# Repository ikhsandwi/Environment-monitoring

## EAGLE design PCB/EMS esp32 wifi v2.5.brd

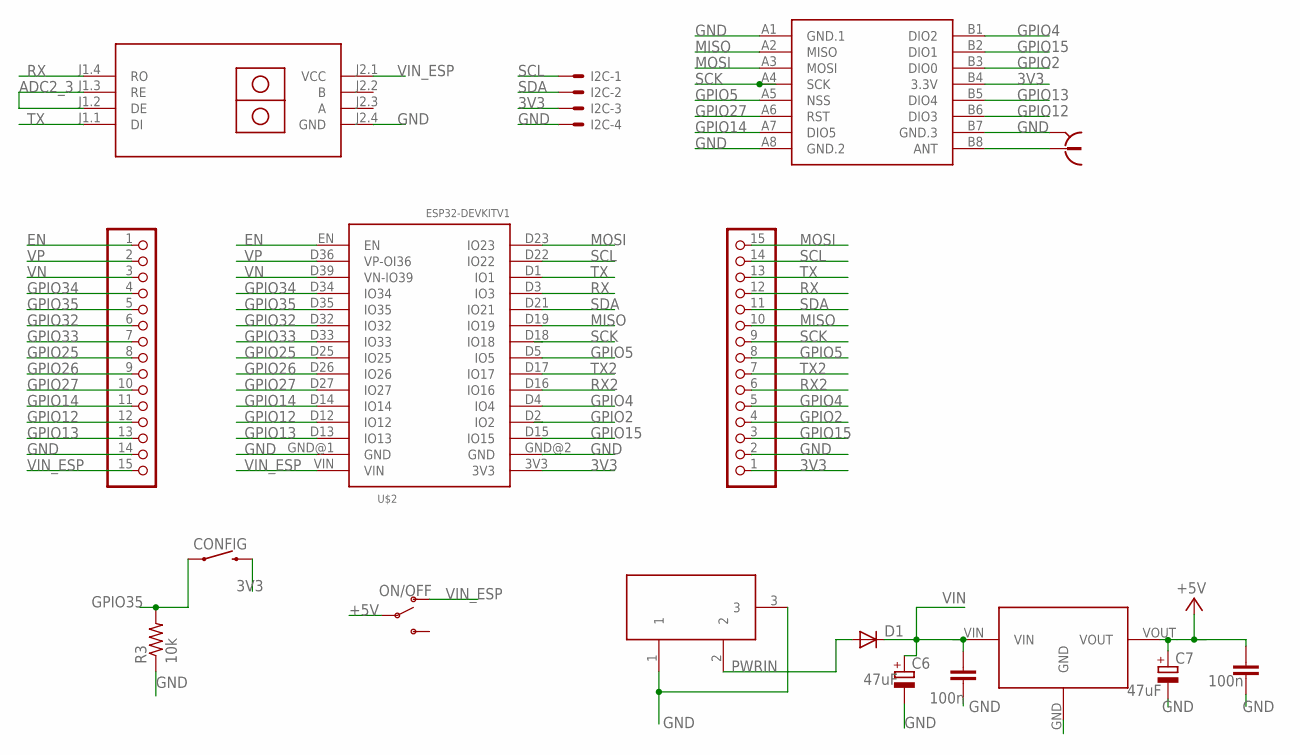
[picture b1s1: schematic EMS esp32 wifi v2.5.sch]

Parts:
C5, C14: 100n; C1206
C6, C7: 47uF; PANASONIC_D
CONFIG: MOMENTARY-SWITCH-SPST-PTH-6.0MM; TACTILE_SWITCH_PTH_6.0MM
D1: DIODE-SMB; SMB
I2C: 22-23-2041
JP1, JP2: PINHD-1X15; 1X15
ON/OFF: SWITCH-SPDT-PTH-11.6X4.0MM; SWITCH_SPDT_PTH_11.6X4.0MM
R3: 10k; 0204/7
U$1: RS485-TTL-CONVERTER
U$2: ESP32DEVKITV1; ESP32-DEVKITV1
U$3: SMARTPRJ_POWERSUPPLY_DC21MMX; SMARTPRJ_POWERSUPPLY_DC-21MM
U$4: 7805-TO263_7805; 7805-TO263_TO263
U$5: WIRELESS-LORA-RFM95W#SMD
X1: 734120110

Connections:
3V3: CONFIG.3 (2), I2C.3, JP2.1, U$2.3V3, U$5.B4 (3.3V)
+5V: C7.+, C14.2, ON/OFF.2, U$4.VOUT
ADC2_3: U$1.J1.2 (DE), U$1.J1.3 (RE)
EN: JP1.1, U$2.EN
GND: C5.1, C6.-, C7.-, C14.1, I2C.4, JP1.14, JP2.2, R3.1, U$1.J2.4 (GND), U$2.GND@1 (GND), U$2.GND@2 (GND), U$3.1, U$3.3, U$4.GND, U$5.A1 (GND.1), U$5.A8 (GND.2), U$5.B7 (GND.3), X1.S@1 (2), X1.S@2 (2), X1.S@3 (2)
GPIO2: JP2.4, U$2.D2 (IO2), U$5.B3 (DIO0)
GPIO4: JP2.5, U$2.D4 (IO4), U$5.B1 (DIO2)
GPIO5: JP2.8, U$2.D5 (IO5), U$5.A5 (NSS)
GPIO12: JP1.12, U$2.D12 (IO12), U$5.B6 (DIO3)
GPIO13: JP1.13, U$2.D13 (IO13), U$5.B5 (DIO4)
GPIO14: JP1.11, U$2.D14 (IO14), U$5.A7 (DIO5)
GPIO15: JP2.3, U$2.D15 (IO15), U$5.B2 (DIO1)
GPIO25: JP1.8, U$2.D25 (IO25)
GPIO26: JP1.9, U$2.D26 (IO26)
GPIO27: JP1.10, U$2.D27 (IO27), U$5.A6 (RST)
GPIO32: JP1.6, U$2.D32 (IO32)
GPIO33: JP1.7, U$2.D33 (IO33)
GPIO34: JP1.4, U$2.D34 (IO34)
GPIO35: CONFIG.1, JP1.5, R3.2, U$2.D35 (IO35)
MISO: JP2.10, U$2.D19 (IO19), U$5.A2 (MISO)
MOSI: JP2.15, U$2.D23 (IO23), U$5.A3 (MOSI)
unnamed: U$5.B8 (ANT), X1.1
PWRIN: D1.A, U$3.2
RX: JP2.12, U$1.J1.4 (RO), U$2.D3 (IO3)
RX2: JP2.6, U$2.D16 (IO16)
SCK: JP2.9, U$2.D18 (IO18), U$5.A4 (SCK)
SCL: I2C.1, JP2.14, U$2.D22 (IO22)
SDA: I2C.2, JP2.11, U$2.D21 (IO21)
TX: JP2.13, U$1.J1.1 (DI), U$2.D1 (IO1)
TX2: JP2.7, U$2.D17 (IO17)
VIN: C5.2, C6.+, D1.C, U$4.VIN
VIN_ESP: JP1.15, ON/OFF.1 (O), U$1.J2.1 (VCC), U$2.VIN
VN: JP1.3, U$2.D39 (VN-IO39)
VP: JP1.2, U$2.D36 (VP-OI36)

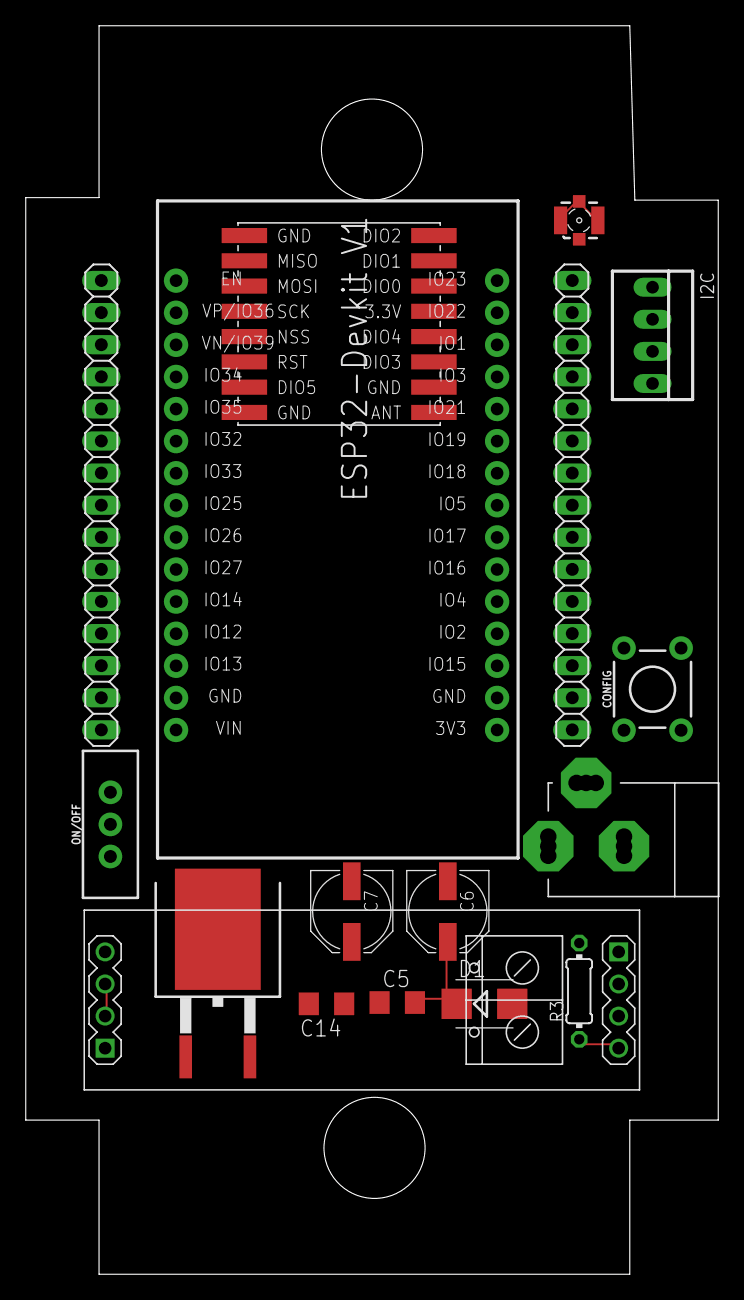
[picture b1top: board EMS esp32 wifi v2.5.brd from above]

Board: 2 copper layers, 54.8 x 98.8 mm, 17 parts (0 on the bottom side), 34 nets.

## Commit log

2020-02-28 environment sensor node LoRa with Antares platform
2020-02-28 read and write modbus RTU & TCP/IP ICPDAS
2020-02-28 upload code & design project
2020-04-14 sensor environment
2020-04-15 wifi config and auto connect
2020-04-16 config wifi + antares

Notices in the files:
parts and their libraries:
diy-modules: Released under the Creative Commons Attribution 4.0 International License: http://creativecommons.org/licenses/by/4.0
SparkFun-Switches: Licensing: Creative Commons ShareAlike 4.0 International - https://creativecommons.org/licenses/by-sa/4.0
